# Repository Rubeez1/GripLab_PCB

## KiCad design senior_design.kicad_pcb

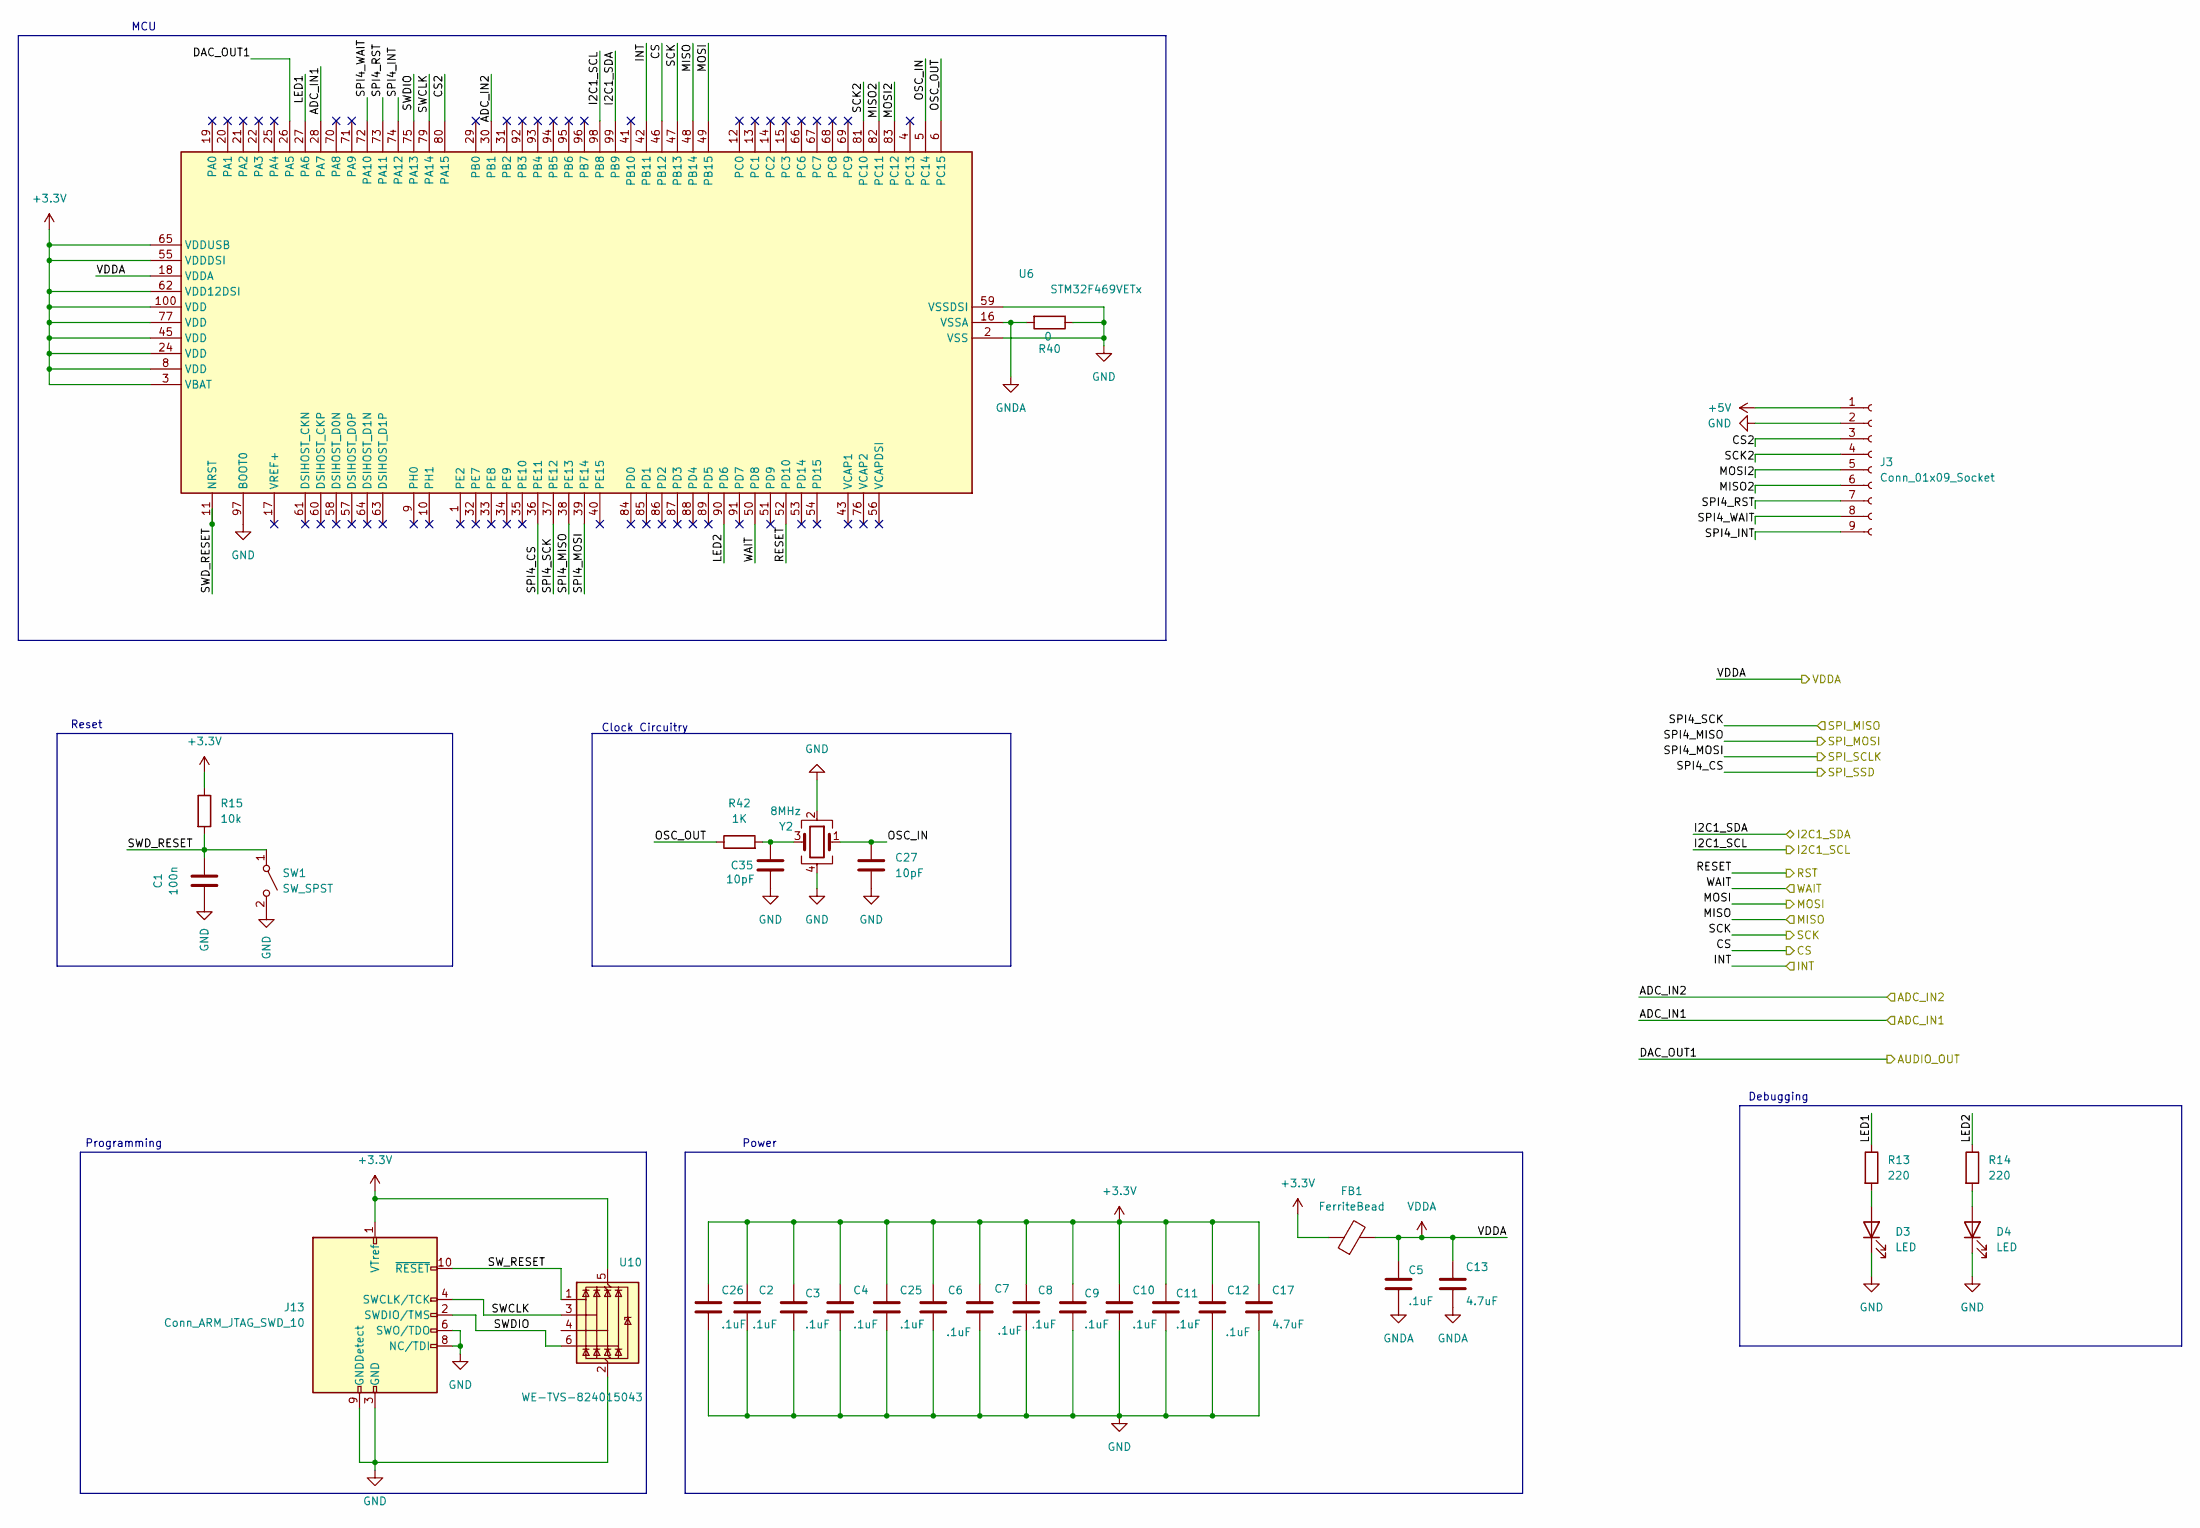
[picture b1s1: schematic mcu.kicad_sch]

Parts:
C1: 100n; C_0805_2012Metric
C2, C3, C4, C5, C6, C7, C8, C9, C10, C11, C12, C25, C26: .1uF; C_0805_2012Metric
C13, C17: 4.7uF; C_0805_2012Metric
C27, C35: 10pF; C_0402_1005Metric
D3, D4: LED; LED_0805_2012Metric
FB1: FerriteBead; LairdTech_28C0236-0JW-10
J3: Conn_01x09_Socket; PinHeader_1x09_P2.00mm_Vertical
J13: Conn_ARM_JTAG_SWD_10; PinSocket_2x05_P2.54mm_Vertical
R13, R14: 220; R_0805_2012Metric
R15: 10k; R_0805_2012Metric
R40: 0; R_0805_2012Metric
R42: 1K; R_0805_2012Metric
SW1: SW_SPST; SW_Push_1P1T_NO_Vertical_Wuerth_434133025816
U6: STM32F469VETx; LQFP-100_14x14mm_P0.5mm
U10: WE-TVS-824015043; SOT-23-6
Y2: 8MHz; Crystal_SMD_SeikoEpson_FA238-4Pin_3.2x2.5mm

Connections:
+3.3V: C2.1, C3.1, C4.1, C6.1, C7.1, C8.1, C9.1, C10.1, C11.1, C12.1, C17.1, C25.1, C26.1, FB1.1, J13.1 (VTref), R15.1, U6.3 (VBAT), U6.8 (VDD), U6.24 (VDD), U6.45 (VDD), U6.55 (VDDDSI), U6.62 (VDD12DSI), U6.65 (VDDUSB), U6.77 (VDD), U6.100 (VDD), U10.5 (VBUS); also elsewhere on the board
+5V: J3.1; also elsewhere on the board
/Audio/AUDIO_IN: U6.26 (PA5); also elsewhere on the board
/Hall Effect/ADC_IN1: U6.28 (PA7); also elsewhere on the board
/Hall Effect/ADC_IN2: U6.30 (PB1); also elsewhere on the board
/MCU/CS: U6.46 (PB12); also elsewhere on the board
/MCU/CS2: J3.3, U6.80 (PA15)
/MCU/I2C1_SCL: U6.98 (PB8); also elsewhere on the board
/MCU/I2C1_SDA: U6.99 (PB9); also elsewhere on the board
/MCU/INT: U6.42 (PB11); also elsewhere on the board
/MCU/LED1: R13.1, U6.27 (PA6)
/MCU/LED2: R14.1, U6.90 (PD6)
/MCU/MISO: U6.48 (PB14); also elsewhere on the board
/MCU/MISO2: J3.6, U6.82 (PC11)
/MCU/MOSI: U6.49 (PB15); also elsewhere on the board
/MCU/MOSI2: J3.5, U6.83 (PC12)
/MCU/OSC_IN: C27.1, U6.5 (PC14), Y2.1
/MCU/OSC_OUT: R42.1, U6.6 (PC15)
/MCU/RESET: U6.52 (PD10); also elsewhere on the board
/MCU/SCK: U6.47 (PB13); also elsewhere on the board
/MCU/SCK2: J3.4, U6.81 (PC10)
/MCU/SPI4_CS: U6.36 (PE11); also elsewhere on the board
/MCU/SPI4_INT: J3.9, U6.74 (PA12)
/MCU/SPI4_MISO: U6.38 (PE13); also elsewhere on the board
/MCU/SPI4_MOSI: U6.39 (PE14); also elsewhere on the board
/MCU/SPI4_RST: J3.7, U6.73 (PA11)
/MCU/SPI4_SCK: U6.37 (PE12); also elsewhere on the board
/MCU/SPI4_WAIT: J3.8, U6.72 (PA10)
/MCU/SWCLK: J13.4 (SWCLK/TCK), U6.79 (PA14), U10.3 (I/O2)
/MCU/SWDIO: J13.2 (SWDIO/TMS), U6.75 (PA13), U10.6 (I/O4)
/MCU/SWD_RESET: C1.2, R15.2, SW1.1 (A), U6.11 (NRST)
/MCU/SW_RESET: J13.10 (~RESET), U10.1 (I/O1)
/MCU/WAIT: U6.50 (PD8); also elsewhere on the board
GND: C1.1, C2.2, C3.2, C4.2, C6.2, C7.2, C8.2, C9.2, C10.2, C11.2, C12.2, C17.2, C25.2, C26.2, C27.2, C35.2, D3.1 (K), D4.1 (K), J3.2, J13.3 (GND), J13.5 (GND), J13.6 (SWO/TDO), J13.8 (NC/TDI), J13.9 (GNDDetect), R40.1, SW1.2 (B), U6.2 (VSS), U6.7 (VSS), U6.23 (VSS), U6.44 (VSS), U6.59 (VSSDSI), U6.78 (VSS), U6.97 (BOOT0), U10.2 (GND), Y2.2, Y2.4; also elsewhere on the board
GNDA: C5.2, C13.2, R40.2, U6.16 (VSSA); also elsewhere on the board
unnamed: C35.1, R42.2, Y2.3
unnamed: D3.2 (A), R13.2
unnamed: D4.2 (A), R14.2
VDDA: C5.1, C13.1, FB1.2, U6.18 (VDDA); also elsewhere on the board

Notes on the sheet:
Programming
Debugging
Power
Reset
MCU
Clock Circuitry

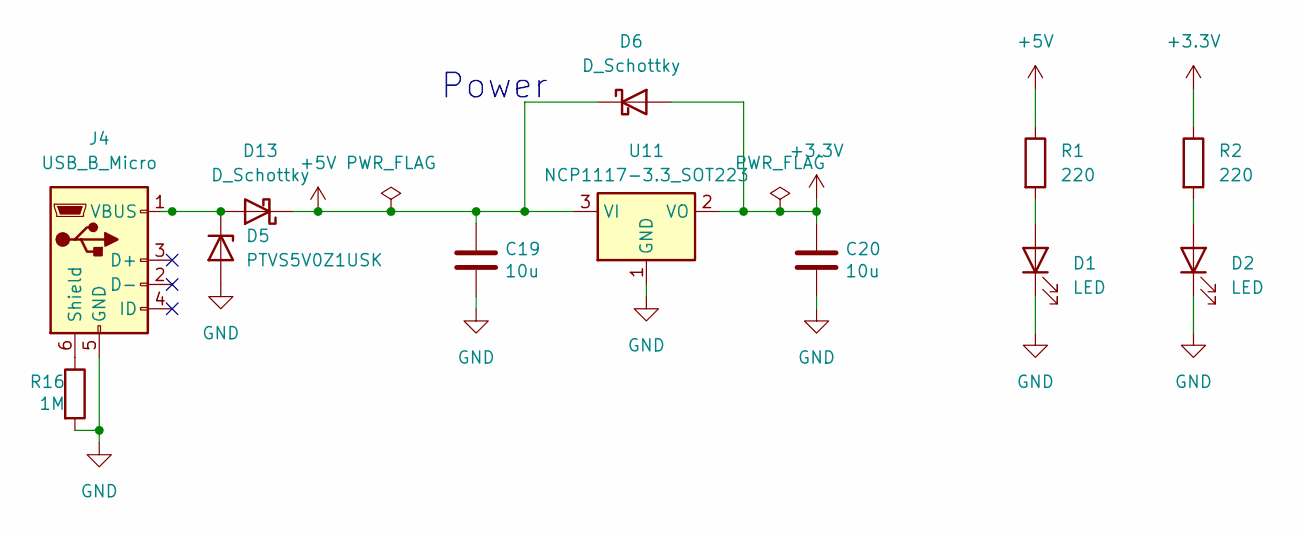
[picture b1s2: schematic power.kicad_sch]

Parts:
C19, C20: 10u; C_0805_2012Metric
D1, D2: LED; LED_0805_2012Metric
D5: PTVS5V0Z1USK; Nexperia_DSN1608-2_1.6x0.8mm
D6, D13: D_Schottky; DIONM4336X250N
J4: USB_B_Micro; USB_Micro-B_Amphenol_10103594-0001LF_Horizontal
R1, R2: 220; R_0805_2012Metric
R16: 1M; R_0805_2012Metric
U11: NCP1117-3.3_SOT223; SOT-223-3_TabPin2

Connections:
+3.3V: C20.1, D6.2 (A), R2.1, U11.2 (VO); also elsewhere on the board
+5V: C19.1, D6.1 (K), D13.1 (K), R1.1, U11.3 (VI); also elsewhere on the board
GND: C19.2, C20.2, D1.1 (K), D2.1 (K), D5.2 (A), J4.5 (GND), R16.2, U11.1 (GND); also elsewhere on the board
unnamed: D1.2 (A), R1.2
unnamed: D2.2 (A), R2.2
unnamed: D5.1 (K), D13.2 (A), J4.1 (VBUS)
unnamed: J4.6 (Shield), R16.1

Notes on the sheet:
Power

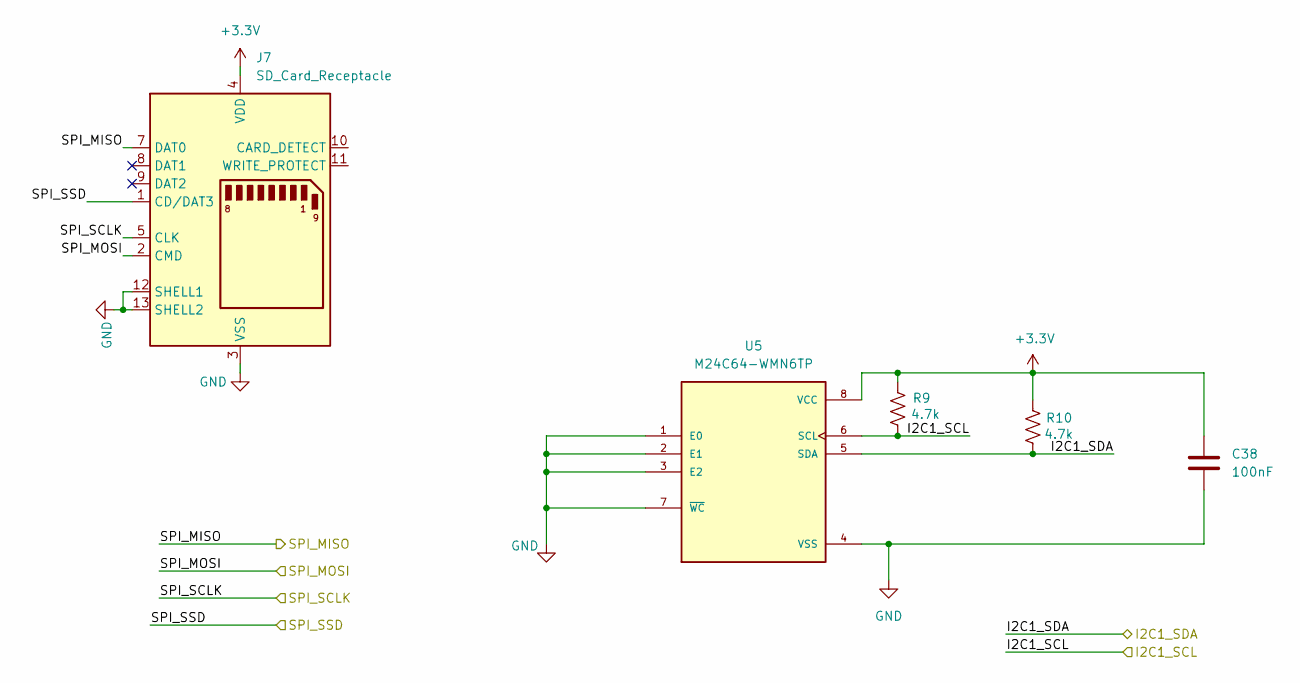
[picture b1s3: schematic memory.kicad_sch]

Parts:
C38: 100nF; C_0805_2012Metric
J7: SD_Card_Receptacle; SD_Kyocera_145638009211859+
R9, R10: 4.7k; R_0805_2012Metric
U5: M24C64-WMN6TP; SOIC127P600X175-8N; PARTREV 38

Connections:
+3.3V: C38.1, J7.4 (VDD), R9.1, R10.1, U5.8 (VCC); also elsewhere on the board
/MCU/I2C1_SCL: R10.2, U5.5 (SDA); also elsewhere on the board
/MCU/I2C1_SDA: R9.2, U5.6 (SCL); also elsewhere on the board
/MCU/SPI4_CS: J7.1 (CD/DAT3); also elsewhere on the board
/MCU/SPI4_MISO: J7.2 (CMD); also elsewhere on the board
/MCU/SPI4_MOSI: J7.5 (CLK); also elsewhere on the board
/MCU/SPI4_SCK: J7.7 (DAT0); also elsewhere on the board
GND: C38.2, J7.3 (VSS), J7.6 (VSS), J7.12 (SHELL1), J7.13 (SHELL2), U5.1 (E0), U5.2 (E1), U5.3 (E2), U5.4 (VSS), U5.7 (~WC); also elsewhere on the board

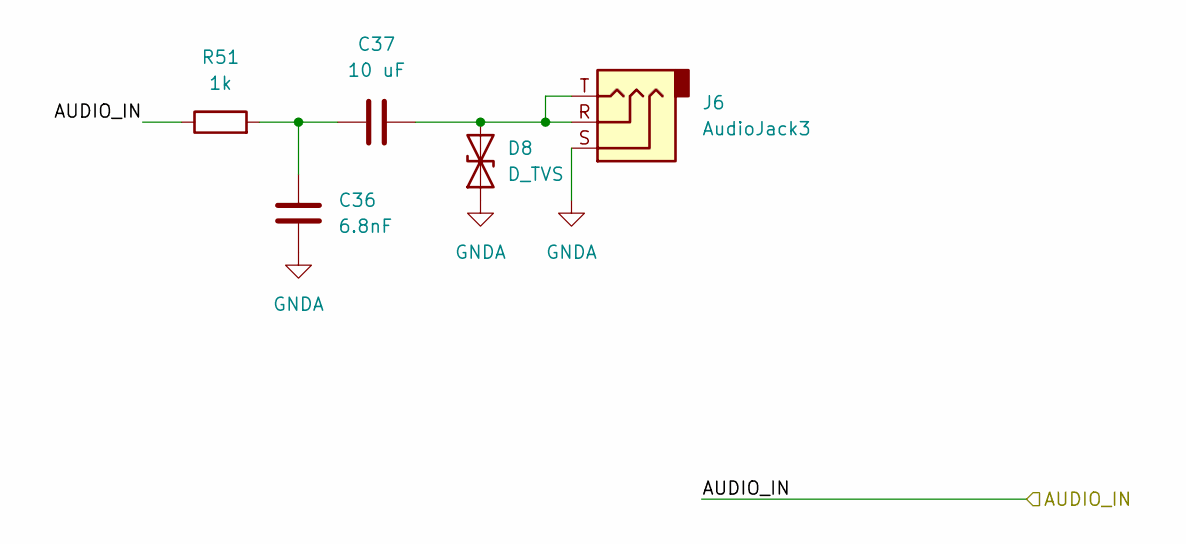
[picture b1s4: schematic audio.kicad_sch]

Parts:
C36: 6.8nF; C_0805_2012Metric_Pad1.18x1.45mm_HandSolder
C37: 10 uF; C_0805_2012Metric_Pad1.18x1.45mm_HandSolder
D8: D_TVS; D_TVS SMB
J6: AudioJack3; Jack_3.5mm_CUI_SJ-3523-SMT_Horizontal
R51: 1k; R_0805_2012Metric_Pad1.20x1.40mm_HandSolder

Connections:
/Audio/AUDIO_IN: R51.1; also elsewhere on the board
GNDA: C36.2, D8.1 (A1), J6.S; also elsewhere on the board
unnamed: C36.1, C37.1, R51.2
unnamed: C37.2, D8.2 (A2), J6.R, J6.T

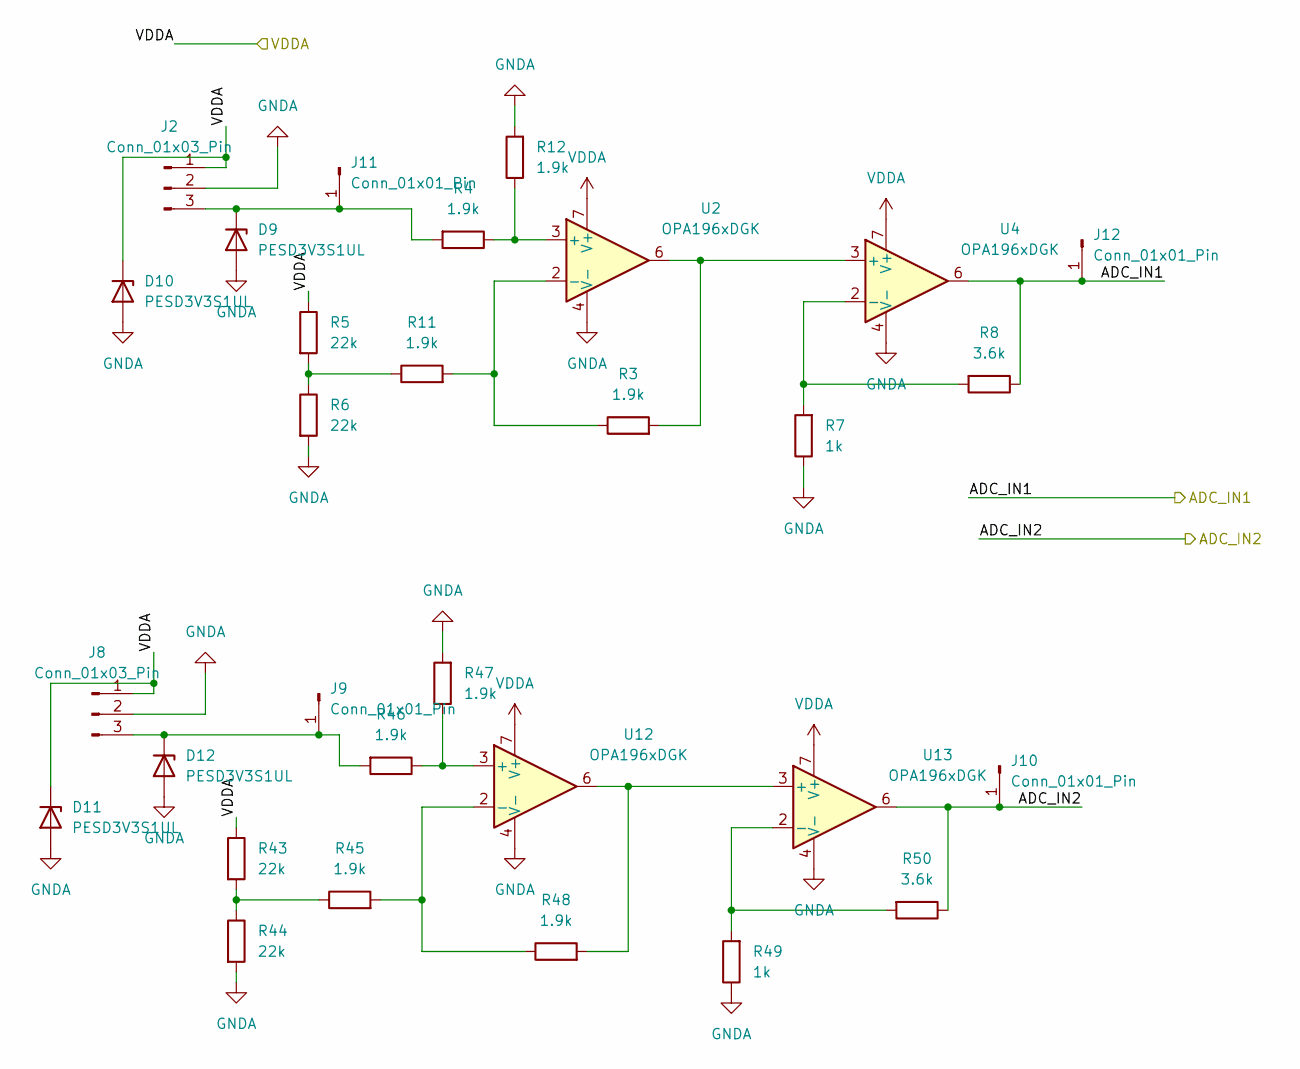
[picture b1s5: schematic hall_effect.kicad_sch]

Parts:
D9, D10, D11, D12: PESD3V3S1UL; D_SOD-882
J2, J8: Conn_01x03_Pin; PinHeader_1x03_P2.54mm_Vertical
J9, J10, J11, J12: Conn_01x01_Pin; PinHeader_1x01_P2.54mm_Vertical
R3, R4, R11, R12, R45, R46, R47, R48: 1.9k; R_0805_2012Metric
R5, R6, R43, R44: 22k; R_0805_2012Metric
R7, R49: 1k; R_0805_2012Metric
R8, R50: 3.6k; R_0805_2012Metric
U2, U4, U12, U13: OPA196xDGK; VSSOP-8_3x3mm_P0.65mm

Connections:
/Hall Effect/ADC_IN1: J12.1, R8.1, U4.6; also elsewhere on the board
/Hall Effect/ADC_IN2: J10.1, R50.1, U13.6; also elsewhere on the board
GNDA: D9.2 (A), D10.2 (A), D11.2 (A), D12.2 (A), J2.2, J8.2, R6.2, R7.1, R12.2, R44.2, R47.2, R49.1, U2.4 (V-), U4.4 (V-), U12.4 (V-), U13.4 (V-); also elsewhere on the board
unnamed: D9.1 (K), J2.3, J11.1, R4.2
unnamed: D12.1 (K), J8.3, J9.1, R46.2
unnamed: R5.2, R6.1, R11.1
unnamed: R43.2, R44.1, R45.1
unnamed: R4.1, R12.1, U2.3 (+)
unnamed: R3.1, R11.2, U2.2 (-)
unnamed: R3.2, U2.6, U4.3 (+)
unnamed: R7.2, R8.2, U4.2 (-)
unnamed: R46.1, R47.1, U12.3 (+)
unnamed: R45.2, R48.1, U12.2 (-)
unnamed: R48.2, U12.6, U13.3 (+)
unnamed: R49.2, R50.2, U13.2 (-)
VDDA: D10.1 (K), D11.1 (K), J2.1, J8.1, R5.1, R43.1, U2.7 (V+), U4.7 (V+), U12.7 (V+), U13.7 (V+); also elsewhere on the board

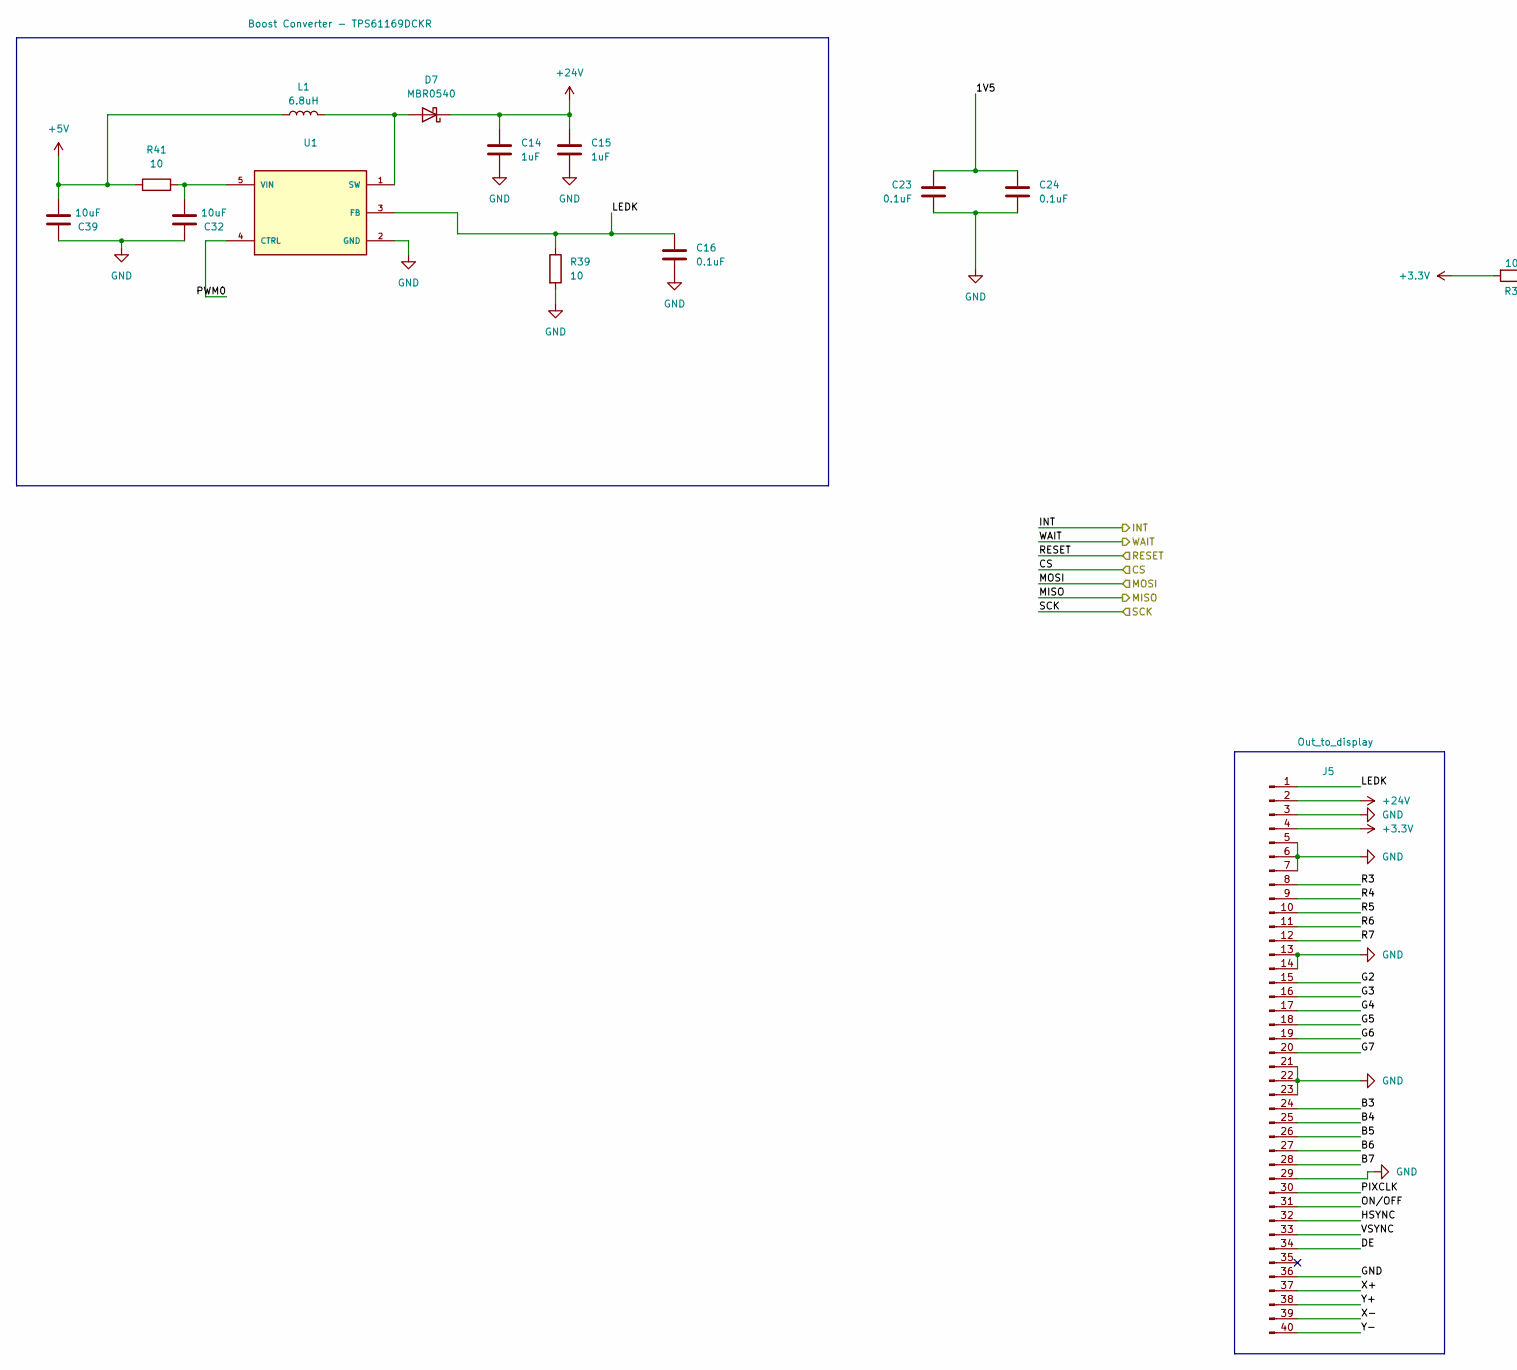
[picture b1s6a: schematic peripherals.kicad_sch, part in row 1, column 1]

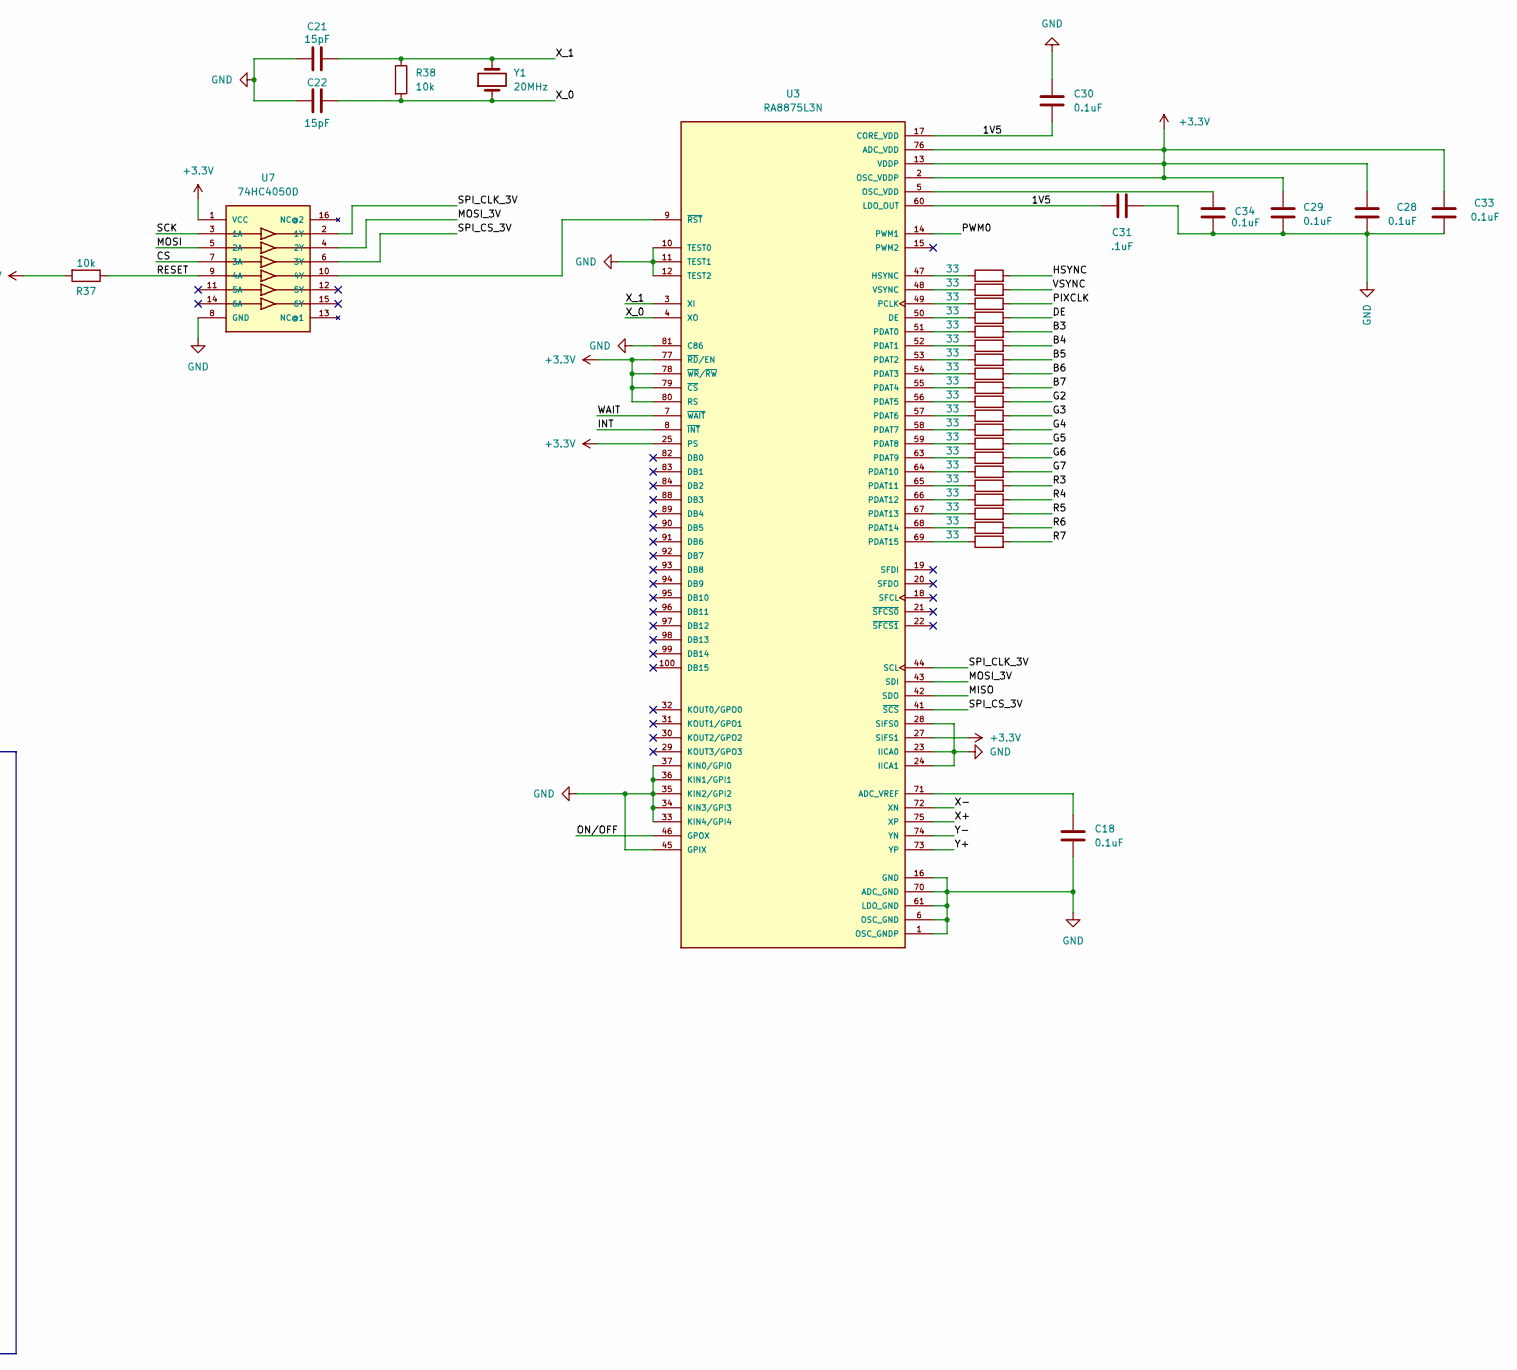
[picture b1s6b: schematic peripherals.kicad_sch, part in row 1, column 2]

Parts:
C14, C15: 1uF; C_0805_2012Metric
C16, C18, C23, C24, C28, C29, C30, C33, C34: 0.1uF; C_0805_2012Metric
C21, C22: 15pF; C_0805_2012Metric
C31: .1uF; C_0805_2012Metric
C32, C39: 10uF; C_0805_2012Metric
D7: MBR0540; D_SOD-123
J5: Out_to_display; Hirose_FH12-40S-0.5SH_1x40-1MP_P0.50mm_Horizontal
L1: 6.8uH; IND_TAIYO_NR5040_TAY
R17, R18, R19, R20, R21, R22, R23, R24, R25, R26, R27, R28, R29, R30, R31, R32, R33, R34, R35, R36: 33; R_0805_2012Metric
R37, R38: 10k; R_0805_2012Metric
R39, R41: 10; R_0805_2012Metric
U1: Boost Converter - TPS61169DCKR; SOT65P210X110-5N; PARTREV A
U3: RA8875L3N; RA8875; PARTREV 1.9
U7: 74HC4050D; SO16
Y1: 20MHz; Crystal_SMD_3225-4Pin_3.2x2.5mm_HandSoldering

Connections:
+3.3V: C28.1, C29.1, C33.1, J5.4, R37.2, U3.2 (OSC_VDDP), U3.13 (VDDP), U3.25 (PS), U3.27 (SIFS1), U3.40 (VDDP), U3.62 (VDDP), U3.76 (ADC_VDD), U3.77 (~RD/EN), U3.78 (~WR/~RW), U3.79 (~CS), U3.80 (RS), U3.87 (VDDP), U7.1 (VCC); also elsewhere on the board
+5V: C39.2, L1.1, R41.1; also elsewhere on the board
+24V: C14.1, C15.1, D7.1 (K), J5.2
/MCU/CS: U7.7 (3A); also elsewhere on the board
/MCU/INT: U3.8 (~INT); also elsewhere on the board
/MCU/MISO: U3.42 (SDO); also elsewhere on the board
/MCU/MOSI: U7.5 (2A); also elsewhere on the board
/MCU/RESET: R37.1, U7.9 (4A); also elsewhere on the board
/MCU/SCK: U7.3 (1A); also elsewhere on the board
/MCU/WAIT: U3.7 (~WAIT); also elsewhere on the board
/Peripherals/B3: J5.24, R17.2
/Peripherals/B4: J5.25, R20.2
/Peripherals/B5: J5.26, R18.2
/Peripherals/B6: J5.27, R19.2
/Peripherals/B7: J5.28, R21.2
/Peripherals/DE: J5.34, R36.2
/Peripherals/G2: J5.15, R22.2
/Peripherals/G3: J5.16, R23.2
/Peripherals/G4: J5.17, R24.2
/Peripherals/G5: J5.18, R25.2
/Peripherals/G6: J5.19, R26.2
/Peripherals/G7: J5.20, R27.2
/Peripherals/HSYNC: J5.32, R33.2
/Peripherals/LEDK: C16.1, J5.1, R39.1, U1.3 (FB)
/Peripherals/MOSI_3V: U3.43 (SDI), U7.4 (2Y)
/Peripherals/ON/OFF: J5.31, U3.46 (GPOX)
/Peripherals/PIXCLK: J5.30, R35.2
/Peripherals/PWM0: U1.4 (CTRL), U3.14 (PWM1)
/Peripherals/R3: J5.8, R28.2
/Peripherals/R4: J5.9, R29.2
/Peripherals/R5: J5.10, R30.2
/Peripherals/R6: J5.11, R31.2
/Peripherals/R7: J5.12, R32.2
/Peripherals/SPI_CLK_3V: U3.44 (SCL), U7.2 (1Y)
/Peripherals/SPI_CS_3V: U3.41 (~SCS), U7.6 (3Y)
/Peripherals/VSYNC: J5.33, R34.2
/Peripherals/X+: J5.37, U3.75 (XP)
/Peripherals/X-: J5.39, U3.72 (XN)
/Peripherals/X_0: C22.2, R38.2, U3.4 (XO), Y1.1
/Peripherals/X_1: C21.2, R38.1, U3.3 (XI), Y1.2
/Peripherals/Y+: J5.38, U3.73 (YP)
/Peripherals/Y-: J5.40, U3.74 (YN)
CORE_VDD: C23.1, C24.1, C30.2, C31.1, U3.17 (CORE_VDD), U3.38 (CORE_VDD), U3.60 (LDO_OUT), U3.86 (CORE_VDD)
GND: C14.2, C15.2, C16.2, C18.2, C21.1, C22.1, C23.2, C24.2, C28.2, C29.2, C30.1, C31.2, C32.1, C33.2, C34.2, C39.1, J5.3, J5.5, J5.6, J5.7, J5.13, J5.14, J5.21, J5.22, J5.23, J5.29, J5.36, R39.2, U1.2 (GND), U3.1 (OSC_GNDP), U3.6 (OSC_GND), U3.10 (TEST0), U3.11 (TEST1), U3.12 (TEST2), U3.16 (GND), U3.23 (IICA0), U3.24 (IICA1), U3.26 (GND), U3.28 (SIFS0), U3.33 (KIN4/GPI4), U3.34 (KIN3/GPI3), U3.35 (KIN2/GPI2), U3.36 (KIN1/GPI1), U3.37 (KIN0/GPI0), U3.39 (GND), U3.45 (GPIX), U3.61 (LDO_GND), U3.70 (ADC_GND), U3.81 (C86), U3.85 (GND), U7.8 (GND); also elsewhere on the board
unnamed: D7.2 (A), L1.2, U1.1 (SW)
unnamed: C32.2, R41.2, U1.5 (VIN)
unnamed: C18.1, U3.71 (ADC_VREF)
unnamed: R36.1, U3.50 (DE)
unnamed: R33.1, U3.47 (HSYNC)
unnamed: C34.1, U3.5 (OSC_VDD)
unnamed: R35.1, U3.49 (PCLK)
unnamed: R17.1, U3.51 (PDAT0)
unnamed: R20.1, U3.52 (PDAT1)
unnamed: R18.1, U3.53 (PDAT2)
unnamed: R19.1, U3.54 (PDAT3)
unnamed: R21.1, U3.55 (PDAT4)
unnamed: R22.1, U3.56 (PDAT5)
unnamed: R23.1, U3.57 (PDAT6)
unnamed: R24.1, U3.58 (PDAT7)
unnamed: R25.1, U3.59 (PDAT8)
unnamed: R26.1, U3.63 (PDAT9)
unnamed: R27.1, U3.64 (PDAT10)
unnamed: R28.1, U3.65 (PDAT11)
unnamed: R29.1, U3.66 (PDAT12)
unnamed: R30.1, U3.67 (PDAT13)
unnamed: R31.1, U3.68 (PDAT14)
unnamed: R32.1, U3.69 (PDAT15)
unnamed: R34.1, U3.48 (VSYNC)
unnamed: U3.9 (~RST), U7.10 (4Y)

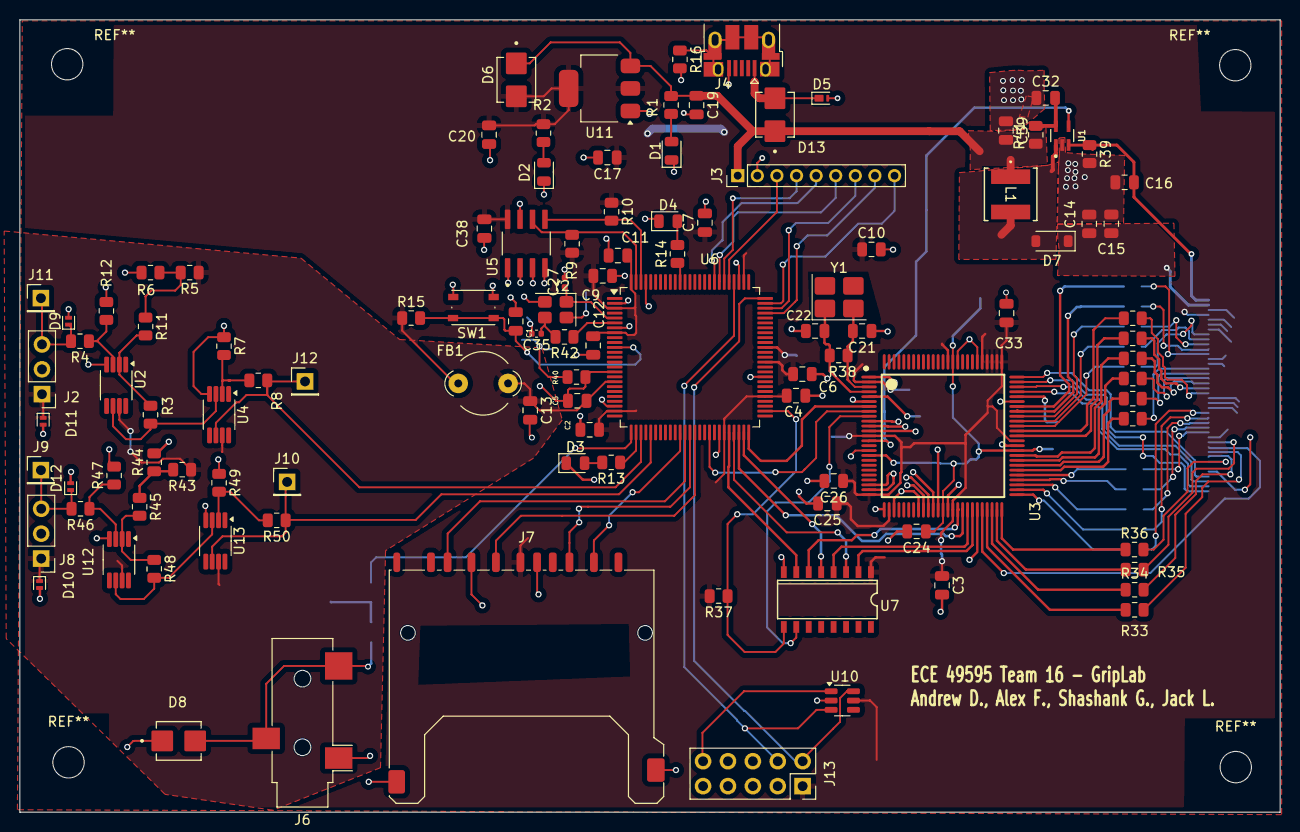
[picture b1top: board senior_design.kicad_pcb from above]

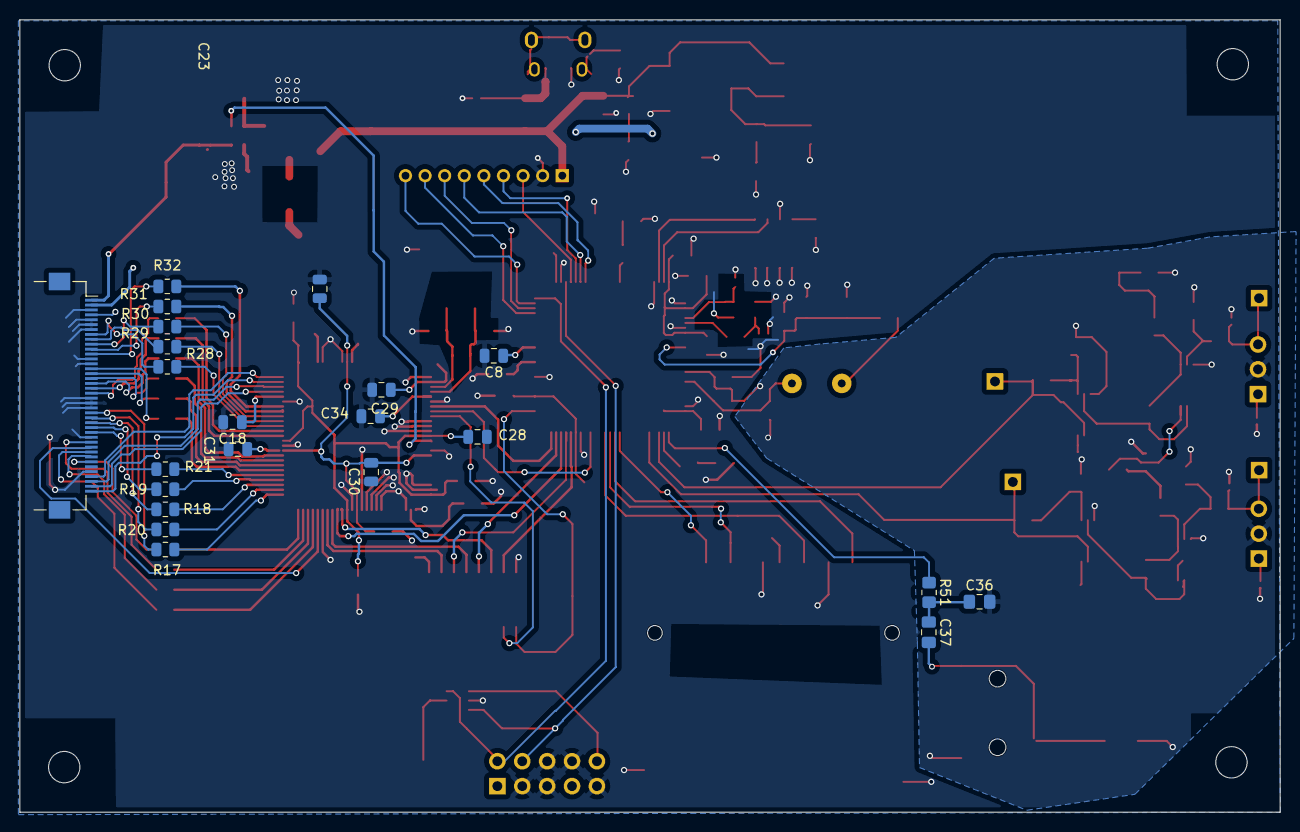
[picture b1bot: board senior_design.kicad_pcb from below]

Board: 2 copper layers, 128.6 x 80.8 mm, 131 parts (22 on the bottom side), 116 nets.

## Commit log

2026-01-31 Add files via upload
    Initial Commit
2026-02-02 Setup Hierarchical Schematic
2026-02-02 added power schematic
2026-02-02 added mcu and SWD connector
2026-02-03 Added EEProm
2026-02-04 Added Pull-Up Resistors to EEProm I2C pins
2026-02-07 changed mcu and added power
2026-02-07 added MCU decaps and hall effect schematic
2026-02-11 layout
2026-02-11 Added footprint library for EEProm
2026-02-11 layout work
2026-02-11 Possibly fixed footprint problem
2026-02-14 cleaned up MCU and added some debugging circuitry
2026-02-15 start of display
2026-02-17 schematic update
2026-02-17 schematic finish
2026-02-18 initial display pcb
2026-02-18 Updated EEProm PCB
2026-02-18 Updated Audio Schematic & PCB
2026-02-18 added memory and fixed clock
2026-02-18 Fixed DRC errors
2026-02-18 Updated Schematic
2026-02-19 Added names on silkscreen and mounting holes
2026-02-25 rearranged HE and SD, added analog power plane
2026-02-25 wired SD card
2026-02-26 re-layout of display subsystem
2026-02-27 added redundent spi
2026-02-27 Updated silkscreen position
2026-02-27 removed lock file
2026-02-27 added HSE
2026-02-27 zip update
2026-02-28 Updated Audio with ESD Diode
2026-03-02 added HE2 and expanded VDDA plane
2026-03-04 fixed a bunch of DRC errors
2026-03-05 added 10 pin stlink and fixed a bunch of errors and warnings
2026-03-09 Some fixes
2026-03-09 shortened data lines
2026-03-09 Fixed labels and added datasheets
2026-03-10 changed spis
2026-03-10 more fixes
2026-03-11 fixed some of the problems
2026-03-11 small fixes
2026-03-11 small changes
2026-03-11 Added constraints
2026-03-11 Updated Constraints for NextPCB
2026-03-11 Boost converter plane edit
2026-03-12 plane and jumper fix
2026-03-12 boost converter
2026-03-12 Feedback Final Update
2026-03-13 fixed several issues from review
2026-03-13 u1 layout fix
2026-03-13 u1 layout fix2
2026-03-13 new archive
2026-03-13 analog plane
2026-03-13 Final Feedback Update
2026-03-13 Gerber & Drill File
